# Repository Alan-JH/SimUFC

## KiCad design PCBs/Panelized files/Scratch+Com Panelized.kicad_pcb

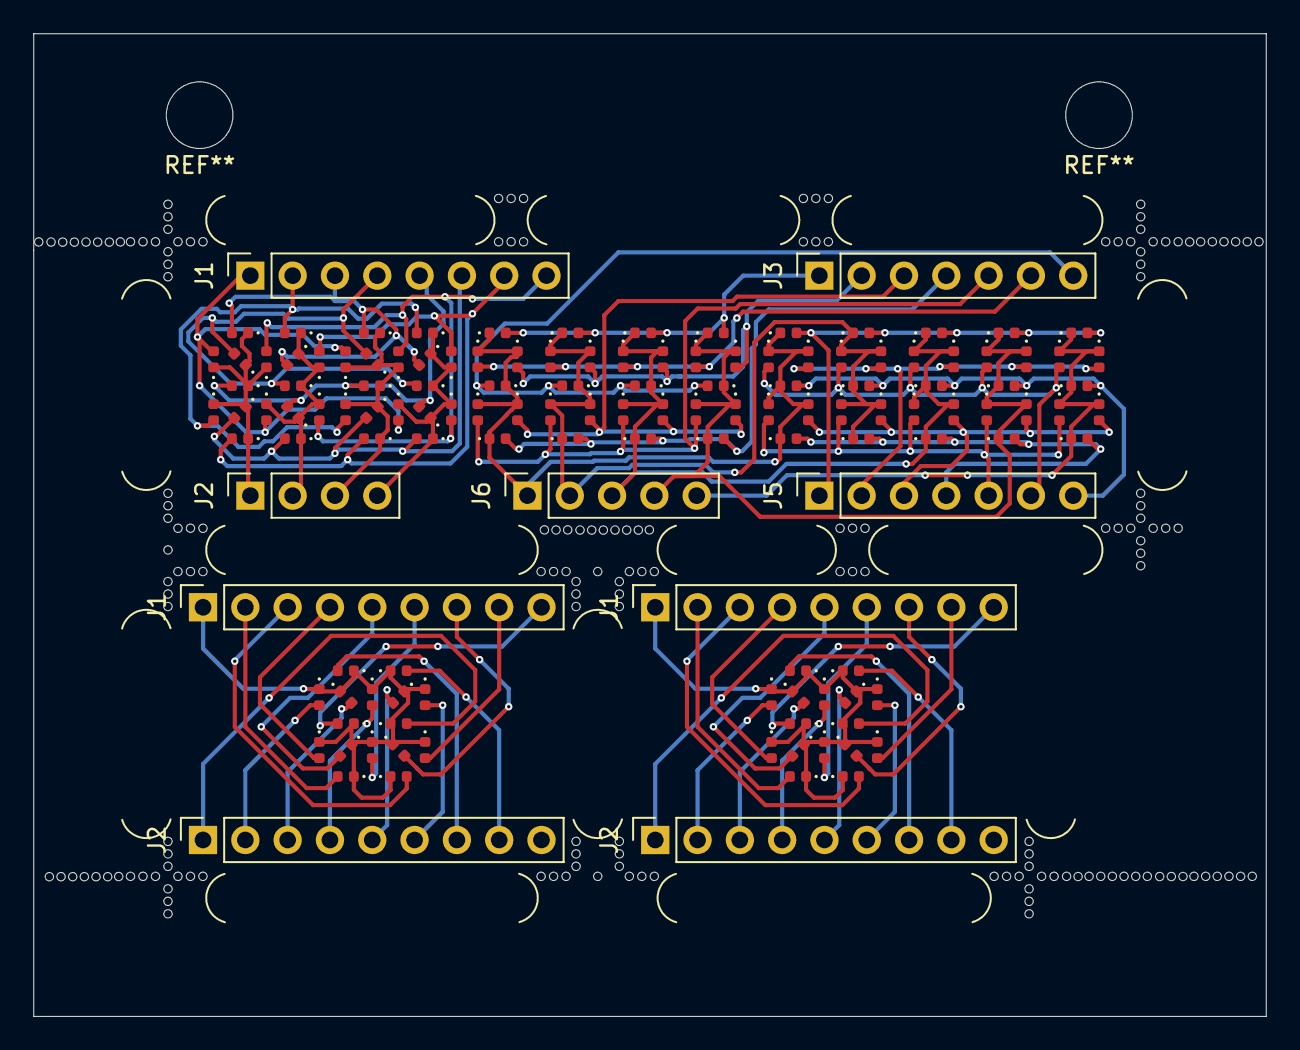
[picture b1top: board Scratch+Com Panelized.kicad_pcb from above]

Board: 2 copper layers, 74.0 x 59.0 mm, 147 parts (0 on the bottom side), 41 nets.

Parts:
D1, D1#2, D1#3, D2, D2#2, D2#3, D3, D3#2, D3#3, D4, D4#2, D4#3, D5, D5#2, D5#3, D6, D6#2, D6#3, D7, D7#2, D7#3, D8, D8#2, D8#3, D9, D9#2, D9#3, D10, D10#2, D10#3, D11, D11#2, D11#3, D12, D12#2, D12#3, D13, D13#2, D13#3, D14, D14#2, D14#3, D15, D15#2, D15#3, D16, D16#2, D16#3, D17, D18, D19, D20, D21, D22, D23, D24, D25, D26, D27, D28, D29, D30, D31, D32, D33, D34, D35, D36, D37, D38, D39, D40, D41, D42, D43, D44, D45, D46, D47, D48, D49, D50, D51, D52, D53, D54, D55, D56, D57, D58, D59, D60, D61, D62, D63, D64, D65, D66, D67, D68, D69, D70, D71, D72, D73, D74, D75, D76, D77, D78, D79, D80, D81, D82, D83, D84, D85, D86, D87, D88, D89, D90, D91, D92, D93, D94, D95: LED; LED_0402_1005Metric
J1: Conn_01x08_Male; PinSocket_1x08_P2.54mm_Vertical
J1#2, J1#3, J2#2, J2#3: Conn_01x09_Male; PinSocket_1x09_P2.54mm_Vertical
J2: Conn_01x04_Male; PinSocket_1x04_P2.54mm_Vertical
J3, J5: Conn_01x07_Male; PinSocket_1x07_P2.54mm_Vertical
J6: Conn_01x05_Male; PinSocket_1x05_P2.54mm_Vertical
mouse-bite-3mm-slot, mouse-bite-3mm-slot#2, mouse-bite-3mm-slot#3: VAL**; mouse-bite-3mm-slot
mouse-bite-3mm-slot-3way, mouse-bite-3mm-slot-3way#2, mouse-bite-3mm-slot-3way#3: VAL**; mouse-bite-3mm-slot-3way
mouse-bite-3mm-slot-corner, mouse-bite-3mm-slot-corner#2, mouse-bite-3mm-slot-corner#3, mouse-bite-3mm-slot-corner#4, mouse-bite-3mm-slot-corner#5: VAL**; mouse-bite-3mm-slot-corner

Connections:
/COM: D1#2.1, D1#3.1, D2#2.1, D2#3.1, D3#2.1, D3#3.1, D4#2.1, D4#3.1, D5#2.1, D5#3.1, D6#2.1, D6#3.1, D7#2.1, D7#3.1, D8#2.1, D8#3.1, D9#2.1, D9#3.1, D10#2.1, D10#3.1, D11#2.1, D11#3.1, D12#2.1, D12#3.1, D13#2.1, D13#3.1, D14#2.1, D14#3.1, D15#2.1, D15#3.1, D16#2.1, D16#3.1, J1#2.1, J1#3.1
/DIG0: D1.1, D2.1, D3.1, D4.1, D5.1, D6.1, D7.1, D8.1, J2.1
/DIG0_2: D33.1, D34.1, D35.1, D36.1, D37.1, D38.1, D39.1, D61.1, D62.1, D63.1, D64.1, D65.1, D66.1, D67.1, J6.1
/DIG1: D9.1, D10.1, D11.1, D12.1, D13.1, D14.1, D15.1, D16.1, J2.2
/DIG1_2: D40.1, D41.1, D42.1, D43.1, D44.1, D45.1, D46.1, D68.1, D69.1, D70.1, D71.1, D72.1, D73.1, D74.1, J6.2
/DIG2: D17.1, D18.1, D19.1, D20.1, D21.1, D22.1, D23.1, D24.1, J2.3
/DIG2_2: D47.1, D48.1, D49.1, D50.1, D51.1, D52.1, D53.1, D75.1, D76.1, D77.1, D78.1, D79.1, D80.1, D81.1, J6.3
/DIG3: D25.1, D26.1, D27.1, D28.1, D29.1, D30.1, D31.1, D32.1, J2.4
/DIG3_2: D54.1, D55.1, D56.1, D57.1, D58.1, D59.1, D60.1, D82.1, D83.1, D84.1, D85.1, D86.1, D87.1, D88.1, J6.4
/DIG4_2: D89.1, D90.1, D91.1, D92.1, D93.1, D94.1, D95.1, J6.5
/SEGA: D1.2, D1#2.2, D1#3.2, D9.2, D17.2, D25.2, J1.1, J1#2.2, J1#3.2
/SEGA2: D33.2, D40.2, D47.2, D54.2, J3.1
/SEGB: D2.2, D2#2.2, D2#3.2, D10.2, D18.2, D26.2, J1.2, J1#2.3, J1#3.3
/SEGB2: D34.2, D41.2, D48.2, D55.2, J3.2
/SEGC: D3.2, D3#2.2, D3#3.2, D11.2, D19.2, D27.2, J1.3, J1#2.4, J1#3.4
/SEGC2: D35.2, D42.2, D49.2, D56.2, J3.3
/SEGD: D4.2, D4#2.2, D4#3.2, D12.2, D20.2, D28.2, J1.4, J1#2.5, J1#3.5
/SEGD2: D36.2, D43.2, D50.2, D57.2, J3.4
/SEGDP: D16#2.2, D16#3.2, J2#2.8, J2#3.8
/SEGE: D5.2, D5#2.2, D5#3.2, D13.2, D21.2, D29.2, J1.5, J1#2.6, J1#3.6
/SEGE2: D37.2, D44.2, D51.2, D58.2, J3.5
/SEGF: D6.2, D6#2.2, D6#3.2, D14.2, D22.2, D30.2, J1.6, J1#2.7, J1#3.7
/SEGF2: D38.2, D45.2, D52.2, D59.2, J3.6
/SEGG: D7.2, D7#2.2, D7#3.2, D15.2, D23.2, D31.2, J1.7, J1#2.8, J1#3.8
/SEGG2: D39.2, D46.2, D53.2, D60.2, J3.7
/SEGH: D8.2, D8#2.2, D8#3.2, D16.2, D24.2, D32.2, J1.8, J1#2.9, J1#3.9
/SEGH2: D61.2, D68.2, D75.2, D82.2, D89.2, J5.1
/SEGJ: D9#2.2, D9#3.2, J2#2.1, J2#3.1
/SEGJ2: D62.2, D69.2, D76.2, D83.2, D90.2, J5.2
/SEGK: D10#2.2, D10#3.2, J2#2.2, J2#3.2
/SEGK2: D63.2, D70.2, D77.2, D84.2, D91.2, J5.3
/SEGL: D11#2.2, D11#3.2, J2#2.3, J2#3.3
/SEGL2: D64.2, D71.2, D78.2, D85.2, D92.2, J5.4
/SEGM: D12#2.2, D12#3.2, J2#2.4, J2#3.4
/SEGM2: D65.2, D72.2, D79.2, D86.2, D93.2, J5.5
/SEGN: D13#2.2, D13#3.2, J2#2.5, J2#3.5
/SEGN2: D66.2, D73.2, D80.2, D87.2, D94.2, J5.6
/SEGP: D14#2.2, D14#3.2, J2#2.6, J2#3.6
/SEGP2: D67.2, D74.2, D81.2, D88.2, D95.2, J5.7
/SEGQ: D15#2.2, D15#3.2, J2#2.7, J2#3.7
unnamed: J2#2.9, J2#3.9

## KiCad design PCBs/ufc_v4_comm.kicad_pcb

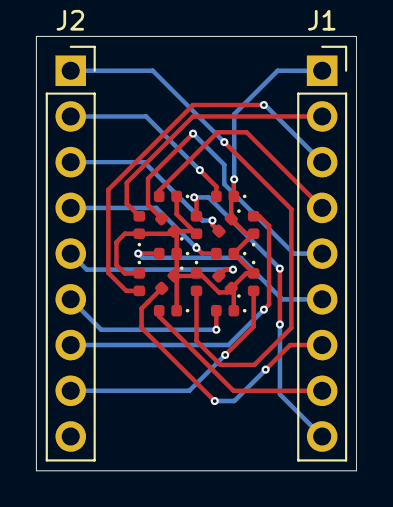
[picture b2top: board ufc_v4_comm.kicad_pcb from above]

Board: 2 copper layers, 17.8 x 24.1 mm, 18 parts (0 on the bottom side), 17 nets.

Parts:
D1, D2, D3, D4, D5, D6, D7, D8, D9, D10, D11, D12, D13, D14, D15, D16: LED; LED_0402_1005Metric
J1, J2: Conn_01x09_Male; PinSocket_1x09_P2.54mm_Vertical

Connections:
/COM: D1.1, D2.1, D3.1, D4.1, D5.1, D6.1, D7.1, D8.1, D9.1, D10.1, D11.1, D12.1, D13.1, D14.1, D15.1, D16.1, J1.1
/SEGA: D1.2, J1.2
/SEGB: D2.2, J1.3
/SEGC: D3.2, J1.4
/SEGD: D4.2, J1.5
/SEGDP: D16.2, J2.8
/SEGE: D5.2, J1.6
/SEGF: D6.2, J1.7
/SEGG: D7.2, J1.8
/SEGH: D8.2, J1.9
/SEGJ: D9.2, J2.1
/SEGK: D10.2, J2.2
/SEGL: D11.2, J2.3
/SEGM: D12.2, J2.4
/SEGN: D13.2, J2.5
/SEGP: D14.2, J2.6
/SEGQ: D15.2, J2.7

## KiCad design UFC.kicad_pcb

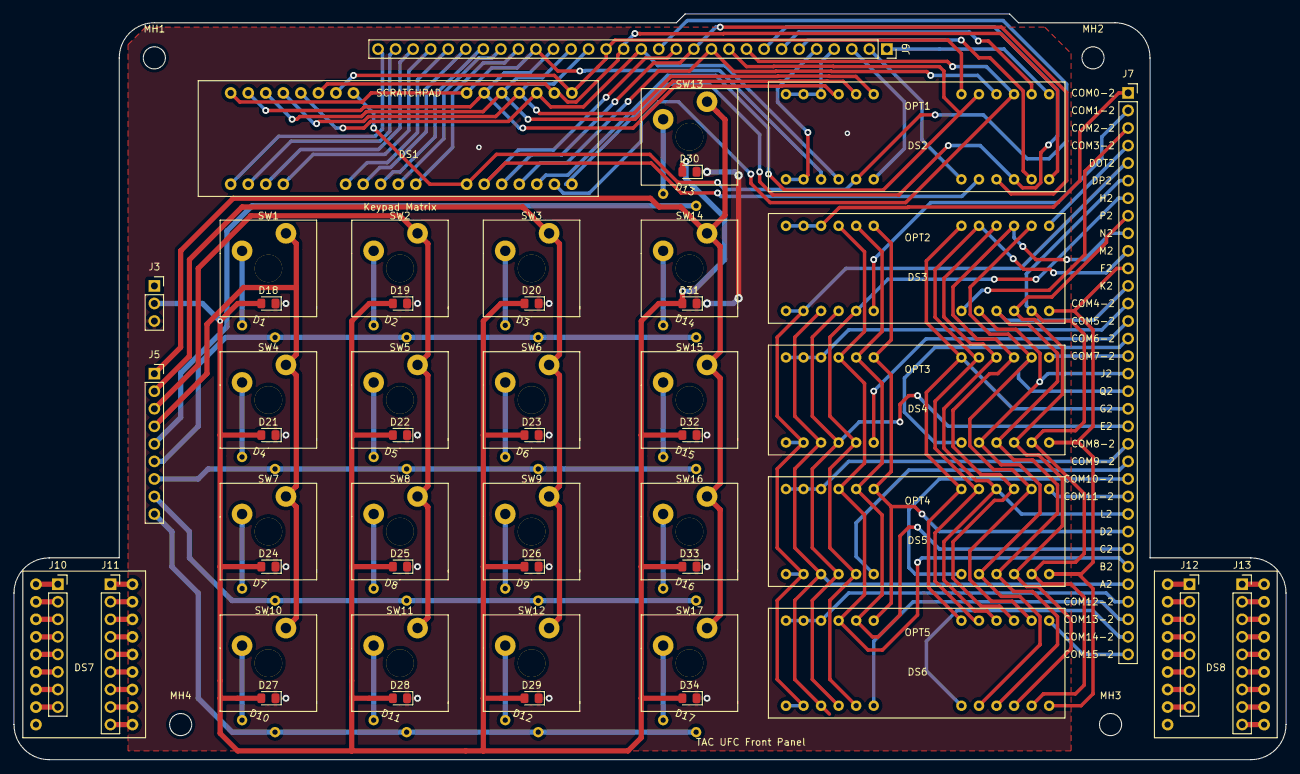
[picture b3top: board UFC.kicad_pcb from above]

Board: 2 copper layers, 184.1 x 108.0 mm, 71 parts (0 on the bottom side), 93 nets.

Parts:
D1, D2, D3, D4, D5, D6, D7, D8, D9, D10, D11, D12, D13, D14, D15, D16, D17: D; 1N4148
D18, D19, D20, D21, D22, D23, D24, D25, D26, D27, D28, D29, D30, D31, D32, D33, D34: LED; LED_0805_2012Metric_Pad1.15x1.40mm_HandSolder
DS1: Scratchpad
DS2, DS3, DS4, DS5, DS6: CustomOptPanel; OPTDisplay
DS7, DS8: CommDS; OHComm
J3: Power; PinSocket_1x03_P2.54mm_Vertical
J5: Matrix; PinSocket_1x09_P2.54mm_Vertical
J7: Driver output 2; PinSocket_1x33_P2.54mm_Vertical
J9: Conn_01x30_Male; PinSocket_1x30_P2.54mm_Vertical
J10, J12: Conn_01x08_Male; PinSocket_1x08_P2.54mm_Vertical
J11, J13: Conn_01x09_Male; PinSocket_1x09_P2.54mm_Vertical
MH1, MH2, MH3, MH4: MountingHole_3.2mm_M3
SW1, SW2, SW3, SW4, SW5, SW6, SW7, SW8, SW9, SW10, SW11, SW12, SW13, SW14, SW15, SW16, SW17: SW_SPST; KailhSW

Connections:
/A1: DS1.1, DS1.9, DS2.15, DS7.2, DS8.2, J9.21, J11.2, J13.2
/A2: DS3.15, DS4.15, DS5.15, DS6.15, J7.29
/B1: DS1.2, DS1.10, DS2.4, DS7.3, DS8.3, J9.20, J11.3, J13.3
/B2: DS3.4, DS4.4, DS5.4, DS6.4, J7.28
/C1: DS1.3, DS1.11, DS2.5, DS7.4, DS8.4, J9.19, J11.4, J13.4
/C2: DS3.5, DS4.5, DS5.5, DS6.5, J7.27
/COL1: J5.4, SW1.2, SW4.2, SW7.2, SW10.2
/COL2: J5.3, SW2.2, SW5.2, SW8.2, SW11.2
/COL3: J5.2, SW3.2, SW6.2, SW9.2, SW12.2
/COL4: J5.1, SW13.2, SW14.2, SW15.2, SW16.2, SW17.2
/COM0-1: DS1.16, J9.30
/COM0-2: DS3.1, DS3.2, DS3.3, J7.1
/COM1-1: DS1.17, J9.29
/COM1-2: DS3.18, J7.2
/COM2-1: DS1.18, J9.28
/COM2-2: DS3.19, J7.3
/COM3-1: DS1.19, J9.27
/COM3-2: DS3.12, J7.4
/COM4-1: DS1.20, J9.26
/COM4-2: DS4.1, DS4.2, DS4.3, J7.13
/COM5-1: DS1.21, J9.25
/COM5-2: DS4.18, J7.14
/COM6-1: DS1.22, J9.24
/COM6-2: DS4.19, J7.15
/COM7-1: DS1.23, J9.23
/COM7-2: DS4.12, J7.16
/COM8-1: DS1.24, J9.22
/COM8-2: DS5.1, DS5.2, DS5.3, J7.21
/COM9-1: DS2.1, DS2.2, DS2.3, J9.4
/COM9-2: DS5.18, J7.22
/COM10-1: DS2.18, J9.3
/COM10-2: DS5.19, J7.23
/COM11-1: DS2.19, J9.2
/COM11-2: DS5.12, J7.24
/COM12-1: DS2.12, J9.1
/COM12-2: DS6.1, DS6.2, DS6.3, J7.30
/COM13-1: DS7.1, J11.1
/COM13-2: DS6.18, J7.31
/COM14-1: DS8.1, J13.1
/COM14-2: DS6.19, J7.32
/COM15-2: DS6.12, J7.33
/D1: DS1.4, DS1.12, DS2.6, DS7.5, DS8.5, J9.18, J11.5, J13.5
/D2: DS3.6, DS4.6, DS5.6, DS6.6, J7.26
/DOT1: DS2.13, DS2.14, J9.5
/DOT2: DS3.13, DS3.14, DS4.13, DS4.14, DS5.13, DS5.14, DS6.13, DS6.14, J7.5
/DP1: DS2.23, DS7.17, DS8.17, J9.6, J10.8, J12.8
/DP2: DS3.23, DS4.23, DS5.23, DS6.23, J7.6
/E1: DS1.5, DS1.13, DS2.16, DS7.6, DS8.6, J9.15, J11.6, J13.6
/E2: DS3.16, DS4.16, DS5.16, DS6.16, J7.20
/F1: DS1.6, DS1.14, DS2.24, DS7.7, DS8.7, J9.16, J11.7, J13.7
/F2: DS3.24, DS4.24, DS5.24, DS6.24, J7.11
/G1: DS1.7, DS1.15, DS2.7, DS7.8, DS8.8, J9.17, J11.8, J13.8
/G2: DS3.7, DS4.7, DS5.7, DS6.7, J7.19
/GND: D18.1, D19.1, D20.1, D21.1, D22.1, D23.1, D24.1, D25.1, D26.1, D27.1, D28.1, D29.1, D30.1, D31.1, D32.1, D33.1, D34.1, J3.3
/H1: DS1.8, DS1.25, DS2.17, DS7.9, DS8.9, J9.14, J11.9, J13.9
/H2: DS3.17, DS4.17, DS5.17, DS6.17, J7.7
/J1: DS1.26, DS2.20, DS7.10, DS8.10, J9.13, J10.1, J12.1
/J2: DS3.20, DS4.20, DS5.20, DS6.20, J7.17
/K1: DS1.27, DS2.21, DS7.11, DS8.11, J9.12, J10.2, J12.2
/K2: DS3.21, DS4.21, DS5.21, DS6.21, J7.12
/L1: DS1.28, DS2.9, DS7.12, DS8.12, J9.11, J10.3, J12.3
/L2: DS3.9, DS4.9, DS5.9, DS6.9, J7.25
/LEDPWM: D18.2, D19.2, D20.2, D21.2, D22.2, D23.2, D24.2, D25.2, D26.2, D27.2, D28.2, D29.2, D30.2, D31.2, D32.2, D33.2, D34.2, J3.2
/M1: DS1.29, DS2.8, DS7.13, DS8.13, J9.10, J10.4, J12.4
/M2: DS3.8, DS4.8, DS5.8, DS6.8, J7.10
/N1: DS1.30, DS2.10, DS7.14, DS8.14, J9.9, J10.5, J12.5
/N2: DS3.10, DS4.10, DS5.10, DS6.10, J7.9
/P1: DS1.31, DS2.22, DS7.15, DS8.15, J9.8, J10.6, J12.6
/P2: DS3.22, DS4.22, DS5.22, DS6.22, J7.8
/Q1: DS2.11, DS7.16, DS8.16, J9.7, J10.7, J12.7
/Q2: DS3.11, DS4.11, DS5.11, DS6.11, J7.18
/ROW0: D13.1, J5.5
/ROW1: D1.1, D2.1, D3.1, D14.1, J5.6
/ROW2: D4.1, D5.1, D6.1, D15.1, J5.7
/ROW3: D7.1, D8.1, D9.1, D16.1, J5.8
/ROW4: D10.1, D11.1, D12.1, D17.1, J5.9
unnamed: D1.2, SW1.1
unnamed: D2.2, SW2.1
unnamed: D3.2, SW3.1
unnamed: D4.2, SW4.1
unnamed: D5.2, SW5.1
unnamed: D6.2, SW6.1
unnamed: D7.2, SW7.1
unnamed: D8.2, SW8.1
unnamed: D9.2, SW9.1
unnamed: D10.2, SW10.1
unnamed: D11.2, SW11.1
unnamed: D12.2, SW12.1
unnamed: D13.2, SW13.1
unnamed: D14.2, SW14.1
unnamed: D15.2, SW15.1
unnamed: D16.2, SW16.1
unnamed: D17.2, SW17.1

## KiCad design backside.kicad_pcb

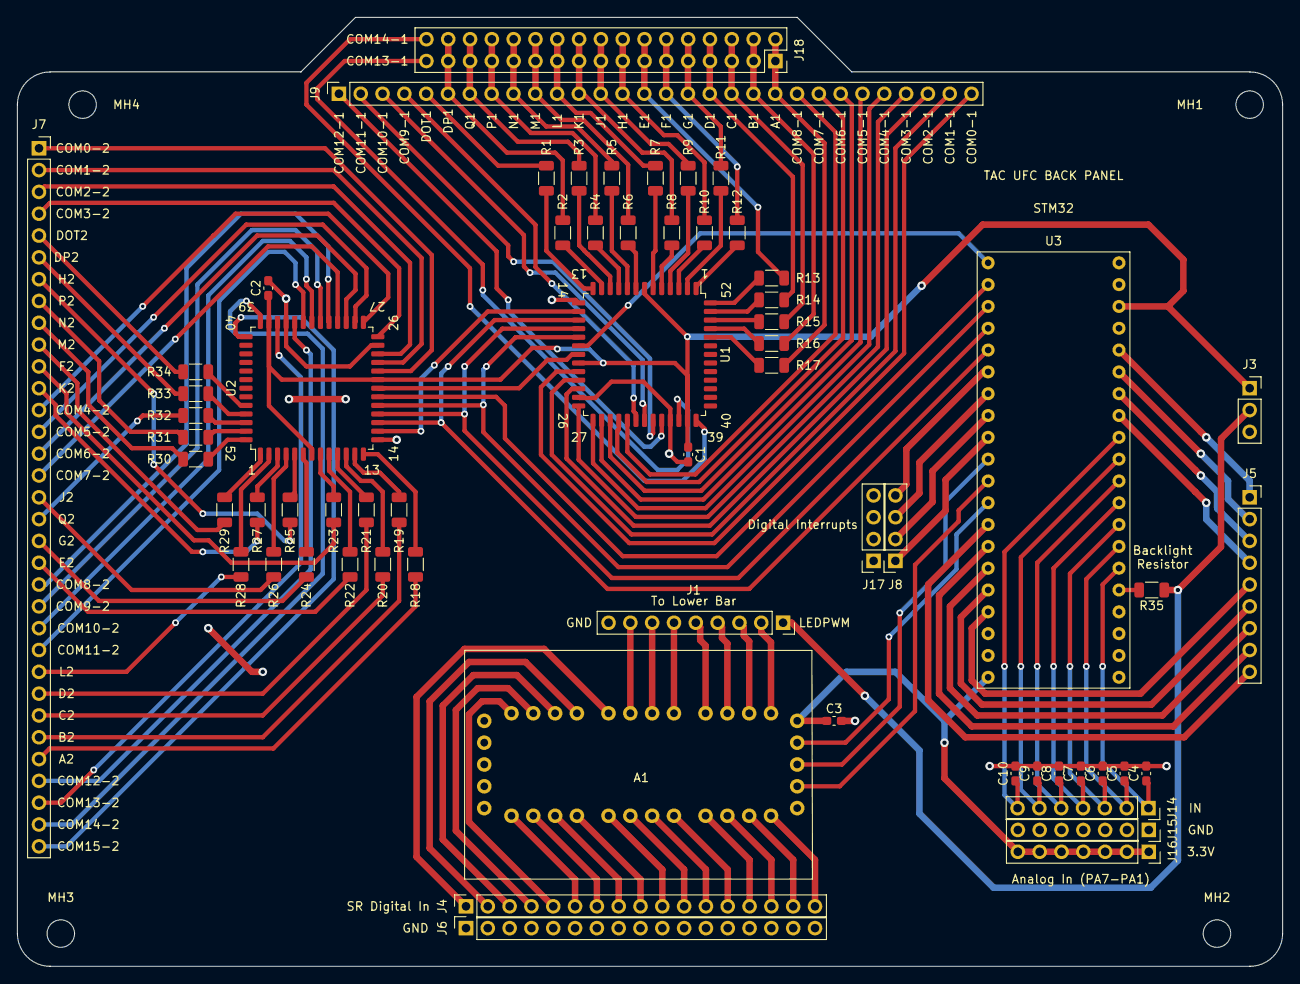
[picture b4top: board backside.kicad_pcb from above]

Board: 2 copper layers, 147.3 x 110.5 mm, 66 parts (0 on the bottom side), 157 nets.

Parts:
A1: ShiftRegisterBoard; ShiftRegisterBoardPins
C1, C2, C3, C4, C5, C6, C7, C8, C9, C10: .1uF; C_0603_1608Metric_Pad1.08x0.95mm_HandSolder
J1: 9Pin; PinSocket_1x09_P2.54mm_Vertical
J3: Power; PinSocket_1x03_P2.54mm_Vertical
J4, J6: Conn_01x17_Male; PinSocket_1x17_P2.54mm_Vertical
J5: Matrix; PinSocket_1x09_P2.54mm_Vertical
J7: Driver output 2; PinSocket_1x33_P2.54mm_Vertical
J8, J17: Conn_01x04_Male; PinSocket_1x04_P2.54mm_Vertical
J9: Conn_01x30_Male; PinSocket_1x30_P2.54mm_Vertical
J14, J15, J16: Conn_01x07_Male; PinSocket_1x07_P2.54mm_Vertical
J18: Conn_02x17_Odd_Even; PinSocket_2x17_P2.54mm_Vertical
MH1, MH2, MH3, MH4: MountingHole_3.2mm_M3
R1, R2, R3, R4, R5, R6, R7, R8, R9, R10, R11, R12, R13, R14, R15, R16, R17, R18, R19, R20, R21, R22, R23, R24, R25, R26, R27, R28, R29, R30, R31, R32, R33, R34: 520R; R_1206_3216Metric
R35: ?; R_1206_3216Metric
U1, U2: HT1632C-52LQFP; LQFP-52_14x14mm_P1mm
U3: STM32F103C8T6; Bluepill

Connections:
/3.3V: A1.10, C1.1, C2.1, C3.1, J3.1, J16.1, J16.2, J16.3, J16.4, J16.5, J16.6, J16.7, U1.7, U1.21, U1.38, U2.7, U2.21, U2.38, U3.47, U3.52
/A1: J9.21, J18.1, J18.2, R17.2
/A2: J7.29, R18.2
/Analog1: C4.1, J14.1, U3.11
/Analog2: C5.1, J14.2, U3.12
/Analog3: C6.1, J14.3, U3.13
/Analog4: C7.1, J14.4, U3.14
/Analog5: C8.1, J14.5, U3.15
/Analog6: C9.1, J14.6, U3.16
/Analog7: C10.1, J14.7, U3.17
/B1: J9.20, J18.3, J18.4, R16.2
/B2: J7.28, R19.2
/C1: J9.19, J18.5, J18.6, R15.2
/C2: J7.27, R20.2
/COL1: J5.4, U3.18
/COL2: J5.3, U3.19
/COL3: J5.2, U3.21
/COL4: J5.1, U3.22
/COM0-1: J9.30, U1.22
/COM0-2: J7.1, U2.22
/COM1-1: J9.29, U1.23
/COM1-2: J7.2, U2.23
/COM2-1: J9.28, U1.24
/COM2-2: J7.3, U2.24
/COM3-1: J9.27, U1.26
/COM3-2: J7.4, U2.26
/COM4-1: J9.26, U1.27
/COM4-2: J7.13, U2.27
/COM5-1: J9.25, U1.28
/COM5-2: J7.14, U2.28
/COM6-1: J9.24, U1.29
/COM6-2: J7.15, U2.29
/COM7-1: J9.23, U1.30
/COM7-2: J7.16, U2.30
/COM8-1: J9.22, U1.31
/COM8-2: J7.21, U2.31
/COM9-1: J9.4, U1.32
/COM9-2: J7.22, U2.32
/COM10-1: J9.3, U1.33
/COM10-2: J7.23, U2.33
/COM11-1: J9.2, U1.34
/COM11-2: J7.24, U2.34
/COM12-1: J9.1, U1.35
/COM12-2: J7.30, U2.35
/COM13-1: J18.33, U1.37
/COM13-2: J7.31, U2.37
/COM14-1: J18.34, U1.39
/COM14-2: J7.32, U2.39
/COM15-2: J7.33, U2.40
/CS1: U1.19, U3.25
/CS2: U2.19, U3.26
/D1: J9.18, J18.7, J18.8, R14.2
/D2: J7.26, R21.2
/DATA: U1.16, U2.16, U3.29
/DIN1: A1.11, J4.6
/DIN2: A1.12, J4.7
/DIN3: A1.13, J4.8
/DIN4: A1.14, J4.9
/DIN5: A1.15, J4.10
/DIN6: A1.16, J4.11
/DIN7: A1.17, J4.12
/DIN8: A1.18, J4.13
/DIN9: A1.19, J4.14
/DIN10: A1.20, J4.15
/DIN11: A1.21, J4.16
/DIN12: A1.22, J4.17
/DIN13: A1.23, J4.5
/DIN14: A1.24, J4.4
/DIN15: A1.25, J4.3
/DIN16: A1.26, J4.2
/DIN17: A1.27, J4.1
/DOT1: J9.5, R1.2
/DOT2: J7.5, R34.2
/DP1: J9.6, J18.31, J18.32, R2.2
/DP2: J7.6, R33.2
/DigInt1: J8.1, U3.33
/DigInt2: J8.2, U3.32
/DigInt3: J8.3, U3.31
/DigInt4: J8.4, U3.30
/E1: J9.15, J18.13, J18.14, R13.2
/E2: J7.20, R22.2
/F1: J9.16, J18.11, J18.12, R12.2
/F2: J7.11, R23.2
/G1: J9.17, J18.9, J18.10, R11.2
/G2: J7.19, R24.2
/GND: A1.1, A1.6, C1.2, C2.2, C3.2, C4.2, C5.2, C6.2, C7.2, C8.2, C9.2, C10.2, J1.9, J3.3, J6.1, J6.2, J6.3, J6.4, J6.5, J6.6, J6.7, J6.8, J6.9, J6.10, J6.11, J6.12, J6.13, J6.14, J6.15, J6.16, J6.17, J15.1, J15.2, J15.3, J15.4, J15.5, J15.6, J15.7, J17.1, J17.2, J17.3, J17.4, U1.14, U1.25, U1.36, U2.14, U2.25, U2.36, U3.48, U3.49, U3.51
/H1: J9.14, J18.15, J18.16, R10.2
/H2: J7.7, R25.2
/J1: J9.13, J18.17, J18.18, R9.2
/J2: J7.17, R26.2
/K1: J9.12, J18.19, J18.20, R8.2
/K2: J7.12, R27.2
/L1: J9.11, J18.21, J18.22, R7.2
/L2: J7.25, R28.2
/LEDPWM: J1.1, J3.2, R35.1
/M1: J9.10, J18.23, J18.24, R6.2
/M2: J7.10, R29.2
/N1: J9.9, J18.25, J18.26, R5.2
/N2: J7.9, R30.2
/OSC: U1.15, U2.15
/P1: J9.8, J18.27, J18.28, R4.2
/P2: J7.8, R31.2
/Q1: J9.7, J18.29, J18.30, R3.2
/Q2: J7.18, R32.2
/RD: U1.18, U2.18, U3.27
/ROW0: J5.5, U3.46
/ROW1: J5.6, U3.45
/ROW2: J5.7, U3.43
/ROW3: J5.8, U3.42
/ROW4: J5.9, U3.41
/SRCLK: A1.7, U3.39
/SRCS: A1.8, U3.38
/SRMISO: A1.9, U3.40
/SW18: A1.28, J1.8
/SW19: A1.29, J1.7
/SW20: A1.30, J1.6
/SW21: A1.31, J1.5
/SW22: A1.32, J1.4
/SW23: A1.33, J1.3
/SW24: A1.34, J1.2
/SYNC: U1.20, U2.20
/WR: U1.17, U2.17, U3.28
unnamed: R1.1, U1.13
unnamed: R2.1, U1.12
unnamed: R3.1, U1.11
unnamed: R4.1, U1.10
unnamed: R5.1, U1.9
unnamed: R6.1, U1.8
unnamed: R7.1, U1.6
unnamed: R8.1, U1.5
unnamed: R9.1, U1.4
unnamed: R10.1, U1.3
unnamed: R11.1, U1.2
unnamed: R12.1, U1.1
unnamed: R13.1, U1.52
unnamed: R14.1, U1.51
unnamed: R15.1, U1.50
unnamed: R16.1, U1.49
unnamed: R17.1, U1.48
unnamed: R18.1, U2.13
unnamed: R19.1, U2.12
unnamed: R20.1, U2.11
unnamed: R21.1, U2.10
unnamed: R22.1, U2.9
unnamed: R23.1, U2.8
unnamed: R24.1, U2.6
unnamed: R25.1, U2.5
unnamed: R26.1, U2.4
unnamed: R27.1, U2.3
unnamed: R28.1, U2.2
unnamed: R29.1, U2.1
unnamed: R30.1, U2.52
unnamed: R31.1, U2.51
unnamed: R32.1, U2.50
unnamed: R33.1, U2.49
unnamed: R34.1, U2.48
unnamed: R35.2, U3.10

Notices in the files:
PCBs/Panelized files/Scratch+Com Panelized.kicad_pcb:
CC BY-NC-SA
